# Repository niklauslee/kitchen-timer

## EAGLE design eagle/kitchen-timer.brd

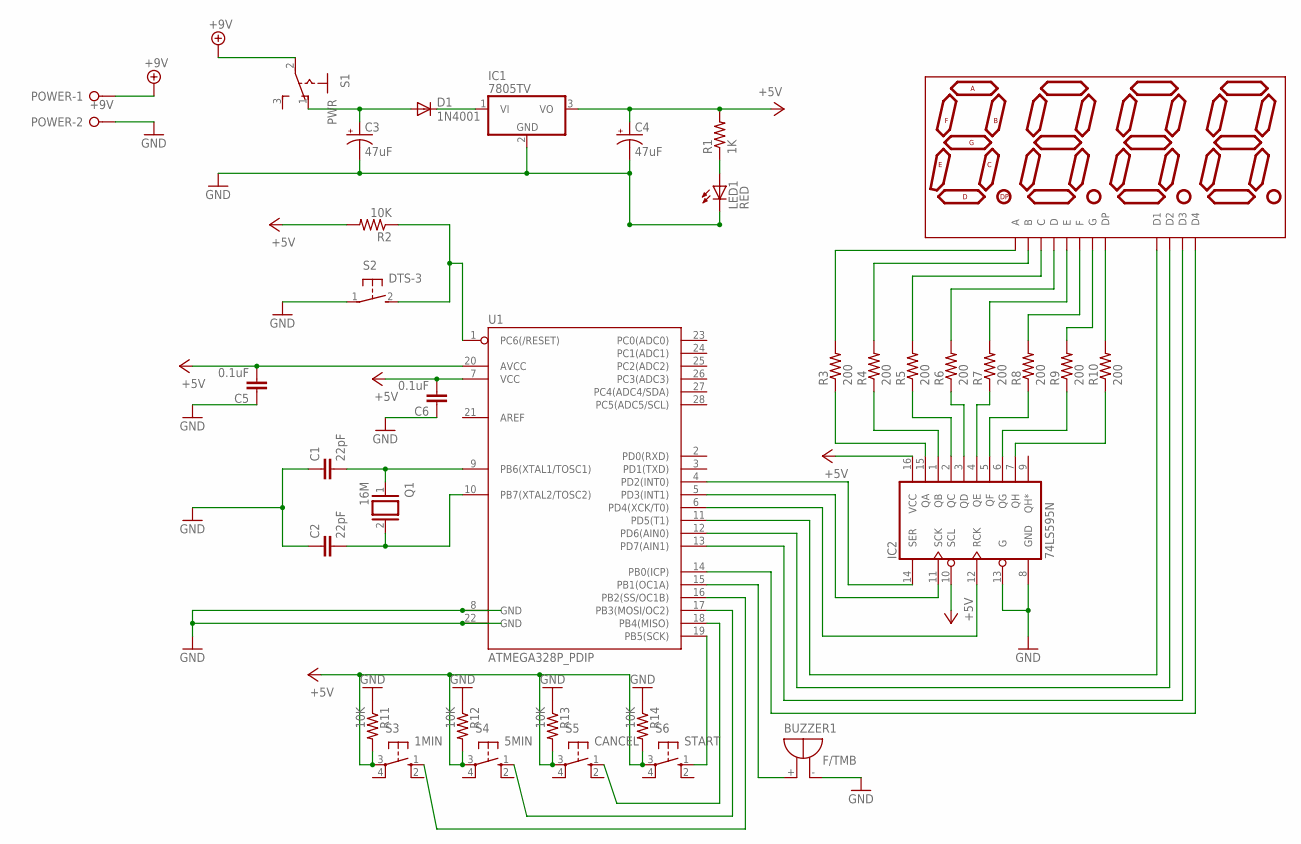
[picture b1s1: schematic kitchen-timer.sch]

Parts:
BUZZER1: F/TMB
C1, C2: 22pF; C025-025X050
C3, C4: 47uF; E2,5-6E
C5, C6: 0.1uF; C025-025X050
D1: 1N4001; D-7.5
DISP1: 7-SEGMENT-4DIGIT-COUNTER-HP-BUBBLE; DIL12
IC1: 7805TV; TO220V
IC2: 74LS595N; DIL16
LED1: RED; LED5MM
POWER: +9V; W237-132
Q1: 16M; QS
R1: 1K; 0204/7
R2, R11, R12, R13, R14: 10K; 0204/7
R3, R4, R5, R6, R7, R8, R9, R10: 200; 0204/7
S1: PWR; 255SB
S2: DTS-3
S3: 1MIN; B3F-10XX
S4: 5MIN; B3F-10XX
S5: CANCEL; B3F-10XX
S6: START; B3F-10XX
U1: ATMEGA328P_PDIP; DIL28-3

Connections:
+5V: C4.+, C5.2, C6.2, IC1.3 (VO), IC2.10 (SCL), IC2.16 (VCC), R1.2, R2.2, R11.2, R12.2, R13.2, R14.2, S3.3, S4.3, S5.3, S6.3, U1.7 (VCC), U1.20 (AVCC)
+9V: POWER.1, S1.2
GND: BUZZER1.-, C1.1, C2.1, C3.-, C4.-, C5.1, C6.1, IC1.2 (GND), IC2.8 (GND), IC2.13 (G), LED1.K (C), POWER.2, R11.1, R12.1, R13.1, R14.1, S2.1, U1.8 (GND), U1.22 (GND)
unnamed: C1.2, Q1.1, U1.9 (PB6(XTAL1/TOSC1))
unnamed: C2.2, Q1.2, U1.10 (PB7(XTAL2/TOSC2))
unnamed: C3.+, D1.A, S1.1 (O)
unnamed: D1.C, IC1.1 (VI)
unnamed: LED1.A, R1.1
unnamed: R2.1, S2.2, U1.1 (PC6(/RESET))
unnamed: IC2.15 (QA), R3.1
unnamed: IC2.1 (QB), R4.1
unnamed: IC2.2 (QC), R5.1
unnamed: IC2.3 (QD), R6.1
unnamed: IC2.4 (QE), R7.1
unnamed: IC2.5 (QF), R8.1
unnamed: IC2.6 (QG), R9.1
unnamed: IC2.7 (QH), R10.1
unnamed: DISP1.5 (DP), R10.2
unnamed: DISP1.7 (G), R9.2
unnamed: DISP1.9 (F), R8.2
unnamed: DISP1.2 (E), R7.2
unnamed: DISP1.8 (D), R6.2
unnamed: DISP1.3 (C), R5.2
unnamed: DISP1.11 (B), R4.2
unnamed: DISP1.12 (A), R3.2
unnamed: IC2.14 (SER), U1.4 (PD2(INT0))
unnamed: IC2.11 (SCK), U1.5 (PD3(INT1))
unnamed: IC2.12 (RCK), U1.6 (PD4(XCK/T0))
unnamed: DISP1.1 (D1), U1.11 (PD5(T1))
unnamed: DISP1.10 (D2), U1.12 (PD6(AIN0))
unnamed: DISP1.4 (D3), U1.13 (PD7(AIN1))
unnamed: DISP1.6 (D4), U1.14 (PB0(ICP))
unnamed: BUZZER1.+, U1.15 (PB1(OC1A))
unnamed: S6.1 (S), U1.19 (PB5(SCK))
unnamed: S5.1 (S), U1.18 (PB4(MISO))
unnamed: S4.1 (S), U1.17 (PB3(MOSI/OC2))
unnamed: S3.1 (S), U1.16 (PB2(SS/OC1B))

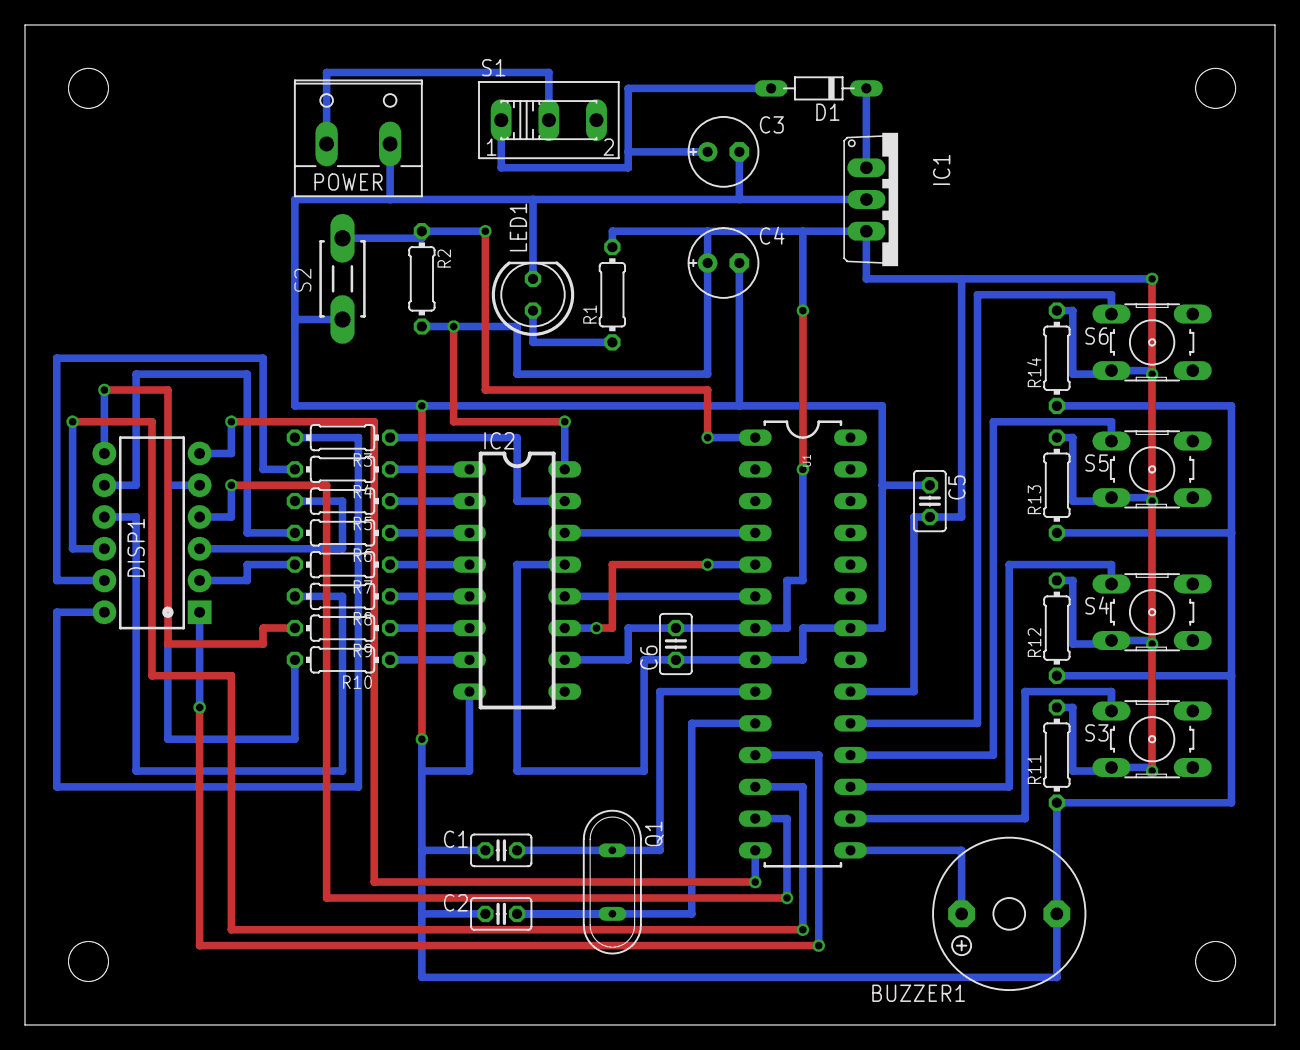
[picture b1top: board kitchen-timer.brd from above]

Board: 2 copper layers, 100.0 x 80.0 mm, 35 parts (0 on the bottom side), 37 nets.

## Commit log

2015-10-05 case design
2015-10-28 button covers

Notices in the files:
parts and their libraries:
SparkFun-DigitalIC: Licensing: Creative Commons ShareAlike 4.0 International - https://creativecommons.org/licenses/by-sa/4.0
